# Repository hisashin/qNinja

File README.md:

# Open Source $300 Real Time PCR and LAMP machine "qNinja"

# $50 qLAMP machine "[qNinja Lite](https://github.com/hisashin/qNinjaLite)" is also available

## Reference Links
- [qNinja portal](https://qninja.hisa.dev)

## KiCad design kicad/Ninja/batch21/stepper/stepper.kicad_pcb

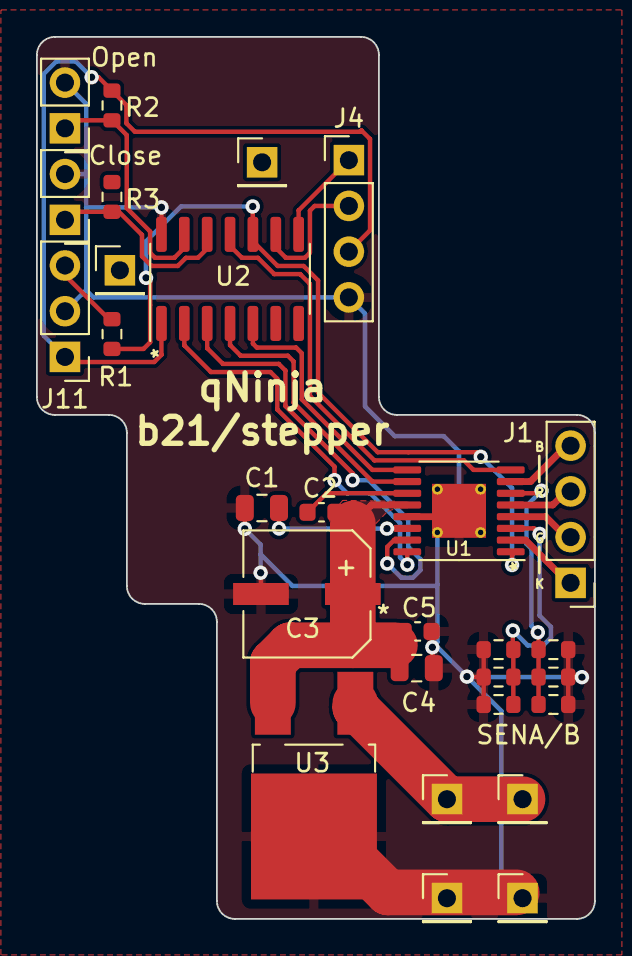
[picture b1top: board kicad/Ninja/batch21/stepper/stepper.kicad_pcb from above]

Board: 2 copper layers, 31.0 x 49.0 mm, 28 parts (0 on the bottom side), 23 nets.

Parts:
C1: 4.7uF; C_0805_2012Metric
C2, C5: 0.1uF; C_0603_1608Metric
C3: 100uF; 35TZV100M6.3X8
C4: 10uF; C_0805_2012Metric
J1: Conn_01x04_Male; PinHeader_1x04_P2.54mm_Vertical
J3, J5, J6, J7, J9, J10: Conn_01x01_Pin; PinHeader_1x01_P2.54mm_Vertical
J4: Conn_01x04_Pin; PinHeader_1x04_P2.54mm_Vertical
J11: Conn_01x03_Pin; PinHeader_1x03_P2.54mm_Vertical
J12, J13: Conn_01x02_Pin; PinHeader_1x02_P2.54mm_Vertical
R1, R2, R3: 4.7k; R_0603_1608Metric
RSENA1, RSENA2, RSENA3: R; R_0603_1608Metric
RSENB1, RSENB2, RSENB3: R; R_0603_1608Metric
U1: MP6507GF-Z; TSSOP-16-1EP_4.4x5mm_P0.65mm_EP3x3mm_ThermalVias
U2: ATtiny404-SS; SOIC-14_3.9x8.7mm_P1.27mm
U3: REG_TO252-3

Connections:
/3V3D: J4.3, J11.1, R2.2, U2.1 (VCC)
/12VB: J5.1, J6.1, U3.1 (VIN)
/AIN1: U1.16 (AIN1), U2.2 (PA4)
/AIN2: U1.15 (AIN2), U2.3 (PA5)
/BIN1: U1.10 (BIN2), U2.4 (PA6)
/BIN2: U1.9 (BIN1), U2.5 (PA7)
/DCLOSE: J13.1, R3.1, U2.12 (PA2)
/DOPEN: J12.1, R2.1, U2.13 (PA3)
/FAULT: U1.8 (FAULT), U2.11 (PA1)
/I2C_SCL: J4.2, U2.9 (PB0)
/I2C_SDA: J4.1, U2.8 (PB1)
/NSLEEP: R1.1, U1.1 (NSLEEP), U2.10 (~RESET/PA0)
/SENA: RSENA1.1, RSENA2.1, RSENA3.1, U1.3 (SENA)
/SENB: RSENB1.2, RSENB2.2, RSENB3.2, U1.6 (SENB)
/UPDI: J11.3, R1.2
/VIN: C2.2, C3.1, C4.1, C5.1, U1.12 (VIN), U3.2 (VOUT)
GND: C1.1, C3.2, C4.2, C5.2, J4.4, J9.1, J10.1, J11.2, J12.2, J13.2, RSENA1.2, RSENA2.2, RSENA3.2, RSENB1.1, RSENB2.1, RSENB3.1, U1.13 (GND), U1.17 (EPAD), U2.14 (GND), U3.3 (GND)
unnamed: J1.1, U1.2 (AOUT1)
unnamed: J1.2, U1.4 (AOUT2)
unnamed: J1.3, U1.5 (BOUT2)
unnamed: J1.4, U1.7 (BOUT1)
unnamed: C2.1, U1.11 (BST)
unnamed: C1.2, U1.14 (VDD)

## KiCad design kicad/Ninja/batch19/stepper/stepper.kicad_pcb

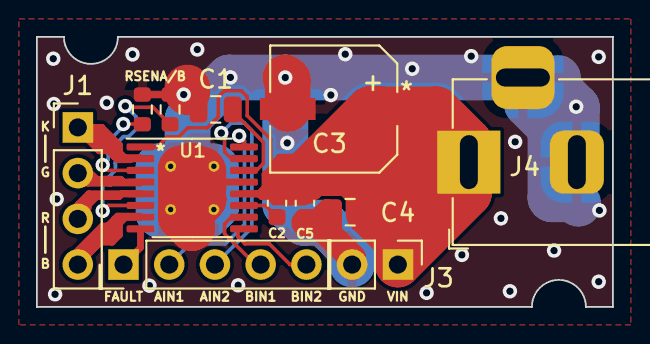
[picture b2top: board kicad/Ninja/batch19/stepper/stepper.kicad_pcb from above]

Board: 2 copper layers, 32.0 x 15.0 mm, 12 parts (0 on the bottom side), 15 nets.

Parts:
C1: 4.7uF; C_0805_2012Metric
C2: 0.1uF; C_0603_1608Metric
C3: 100uF; 35TZV100M6.3X8
C4: 10uF; C_0805_2012Metric
C5: 0.1uF(Low ESR ceramic); C_0603_1608Metric
J1: Conn_01x04_Male; PinHeader_1x04_P2.54mm_Vertical
J2: Conn_01x05_Male; PinHeader_1x05_P2.54mm_Vertical
J3: Conn_01x02_Male; PinHeader_1x02_P2.54mm_Vertical
J4: Barrel_Jack_Switch; BarrelJack_Horizontal
RSENA1: R; R_0603_1608Metric
RSENB1: R; R_0603_1608Metric
U1: MP6507GF-Z; TSSOP-16-1EP_4.4x5mm_P0.65mm_EP3x3mm_ThermalVias

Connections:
/AIN1: J2.2, U1.16 (AIN1)
/AIN2: J2.3, U1.15 (AIN2)
/BIN1: J2.4, U1.10 (BIN2)
/BIN2: J2.5, U1.9 (BIN1)
/FAULT: J2.1, U1.8 (FAULT)
/VIN: C2.2, C3.1, C4.1, C5.1, J3.1, J4.1, U1.1 (NSLEEP), U1.12 (VIN)
GND: C1.1, C3.2, C4.2, C5.2, J3.2, J4.2, J4.3, RSENA1.2, RSENB1.2, U1.13 (GND), U1.17 (EPAD)
unnamed: C1.2, U1.14 (VDD)
unnamed: C2.1, U1.11 (BST)
unnamed: J1.1, U1.2 (AOUT1)
unnamed: J1.2, U1.4 (AOUT2)
unnamed: J1.3, U1.5 (BOUT2)
unnamed: J1.4, U1.7 (BOUT1)
unnamed: RSENA1.1, U1.3 (SENA)
unnamed: RSENB1.1, U1.6 (SENB)

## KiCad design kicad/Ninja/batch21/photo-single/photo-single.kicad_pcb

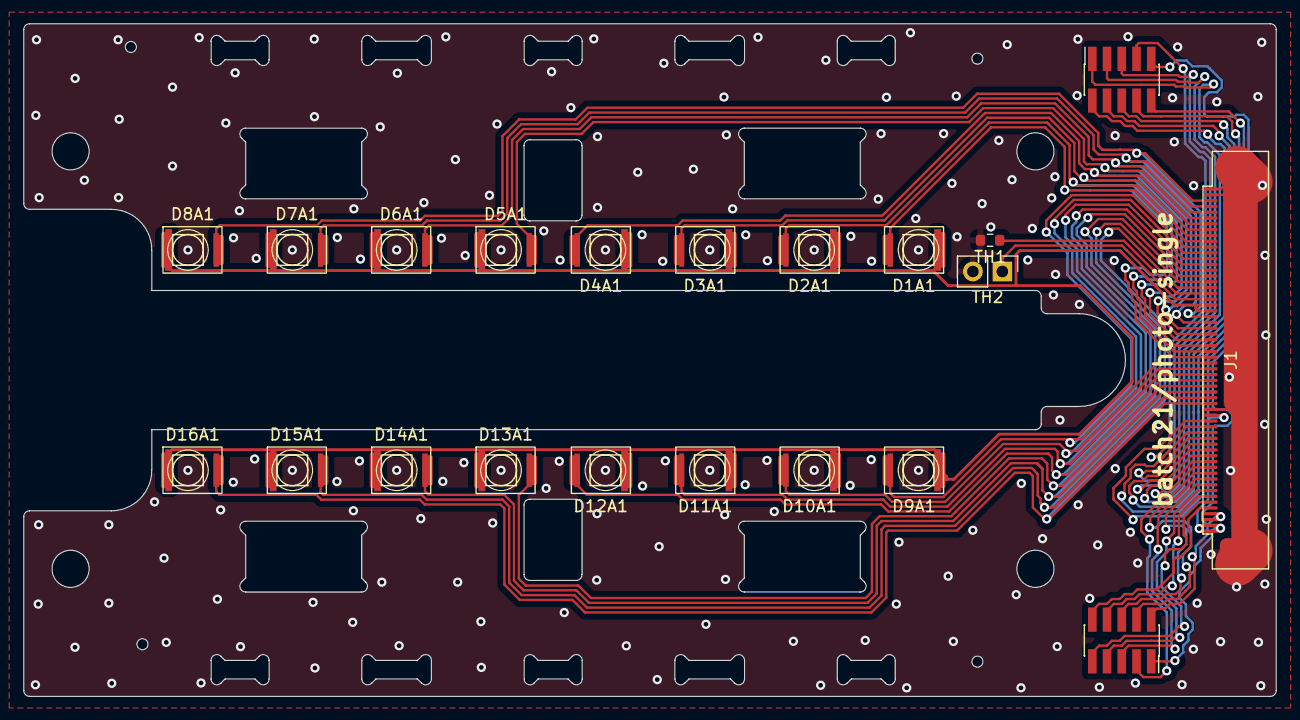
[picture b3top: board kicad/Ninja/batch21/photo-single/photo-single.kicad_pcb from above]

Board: 2 copper layers, 108.0 x 58.0 mm, 21 parts (0 on the bottom side), 38 nets.

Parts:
D1A1, D2A1, D3A1, D4A1, D5A1, D6A1, D7A1, D8A1, D9A1, D10A1, D11A1, D12A1, D13A1, D14A1, D15A1, D16A1: D_Photo; SFH2200_2201_2240
J1: Conn_01x60_Male; FFC_60_Ali_HUISHUNFA
JLN1: Conn_01x10_Male; PinSocket_2x05_P1.27mm_Vertical_SMD
JLS1: Conn_01x10_Male; PinSocket_2x05_P1.27mm_Vertical_SMD
TH1: Thermistor; R_0603_1608Metric
TH2: Thermistor; PinHeader_1x02_P2.54mm_Vertical

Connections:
/N_LED_OUT1: J1.20, JLN1.8
/N_LED_OUT2: J1.19, JLN1.7
/N_LED_OUT3: J1.18, JLN1.6
/N_LED_OUT4: J1.17, JLN1.5
/N_LED_OUT5: J1.16, JLN1.4
/N_LED_OUT6: J1.15, JLN1.3
/N_LED_OUT7: J1.14, JLN1.2
/N_LED_OUT8: J1.13, JLN1.1
/N_PD_OUT1: D1A1.2 (A), J1.31, J1.51
/N_PD_OUT3: D2A1.2 (A), J1.32, J1.52
/N_PD_OUT5: D3A1.2 (A), J1.33, J1.53
/N_PD_OUT7: D4A1.2 (A), J1.34, J1.54
/N_PD_OUT9: D5A1.2 (A), J1.35, J1.55
/N_PD_OUT11: D6A1.2 (A), J1.36, J1.56
/N_PD_OUT13: D7A1.2 (A), J1.37, J1.57
/N_PD_OUT15: D8A1.2 (A), J1.38, J1.58
/S_LED_OUT1: J1.12, JLS1.3
/S_LED_OUT2: J1.11, JLS1.4
/S_LED_OUT3: J1.10, JLS1.5
/S_LED_OUT4: J1.9, JLS1.6
/S_LED_OUT5: J1.8, JLS1.7
/S_LED_OUT6: J1.7, JLS1.8
/S_LED_OUT7: J1.6, JLS1.9
/S_LED_OUT8: J1.5, JLS1.10
/S_PD_OUT1: D9A1.2 (A), J1.30, J1.50
/S_PD_OUT3: D10A1.2 (A), J1.29, J1.49
/S_PD_OUT5: D11A1.2 (A), J1.28, J1.48
/S_PD_OUT7: D12A1.2 (A), J1.27, J1.47
/S_PD_OUT9: D13A1.2 (A), J1.26, J1.46
/S_PD_OUT11: D14A1.2 (A), J1.25, J1.45
/S_PD_OUT13: D15A1.2 (A), J1.24, J1.44
/S_PD_OUT15: D16A1.2 (A), J1.23, J1.43
GNDA: J1.22, J1.59, J1.60, J1.G1, J1.G2, TH1.2, TH2.2
GNDL: J1.1, J1.2, J1.21, JLN1.10, JLS1.1
unnamed: J1.41, TH2.1
unnamed: J1.42, TH1.1
VCCA: D1A1.1 (K), D2A1.1 (K), D3A1.1 (K), D4A1.1 (K), D5A1.1 (K), D6A1.1 (K), D7A1.1 (K), D8A1.1 (K), D9A1.1 (K), D10A1.1 (K), D11A1.1 (K), D12A1.1 (K), D13A1.1 (K), D14A1.1 (K), D15A1.1 (K), D16A1.1 (K), J1.39, J1.40
VCCL: J1.3, J1.4, JLN1.9, JLS1.2

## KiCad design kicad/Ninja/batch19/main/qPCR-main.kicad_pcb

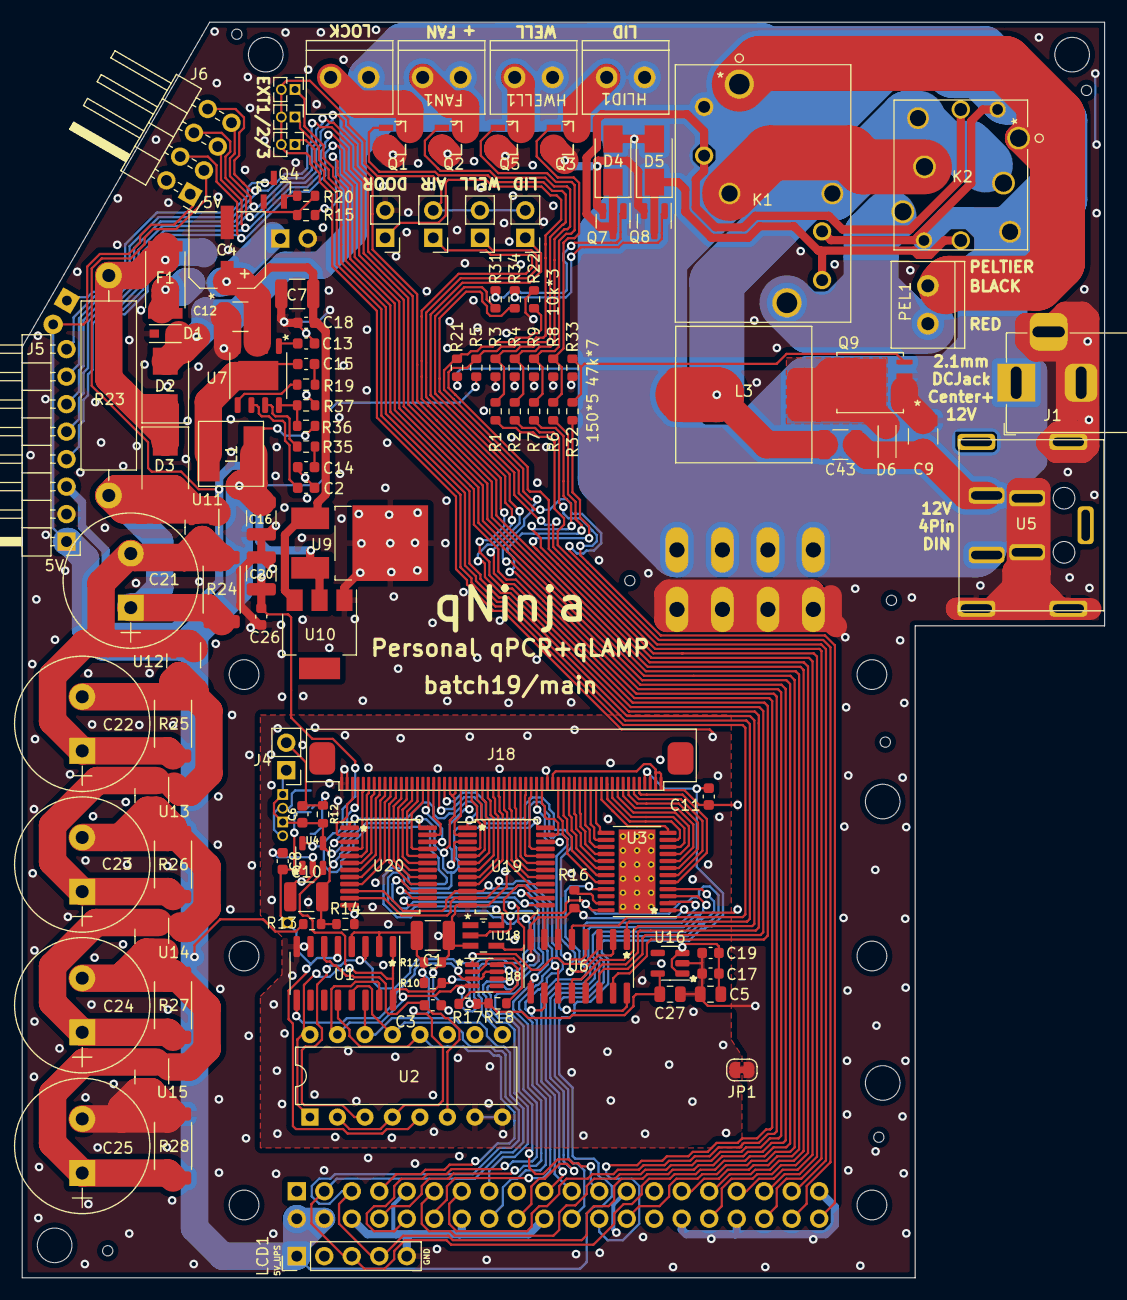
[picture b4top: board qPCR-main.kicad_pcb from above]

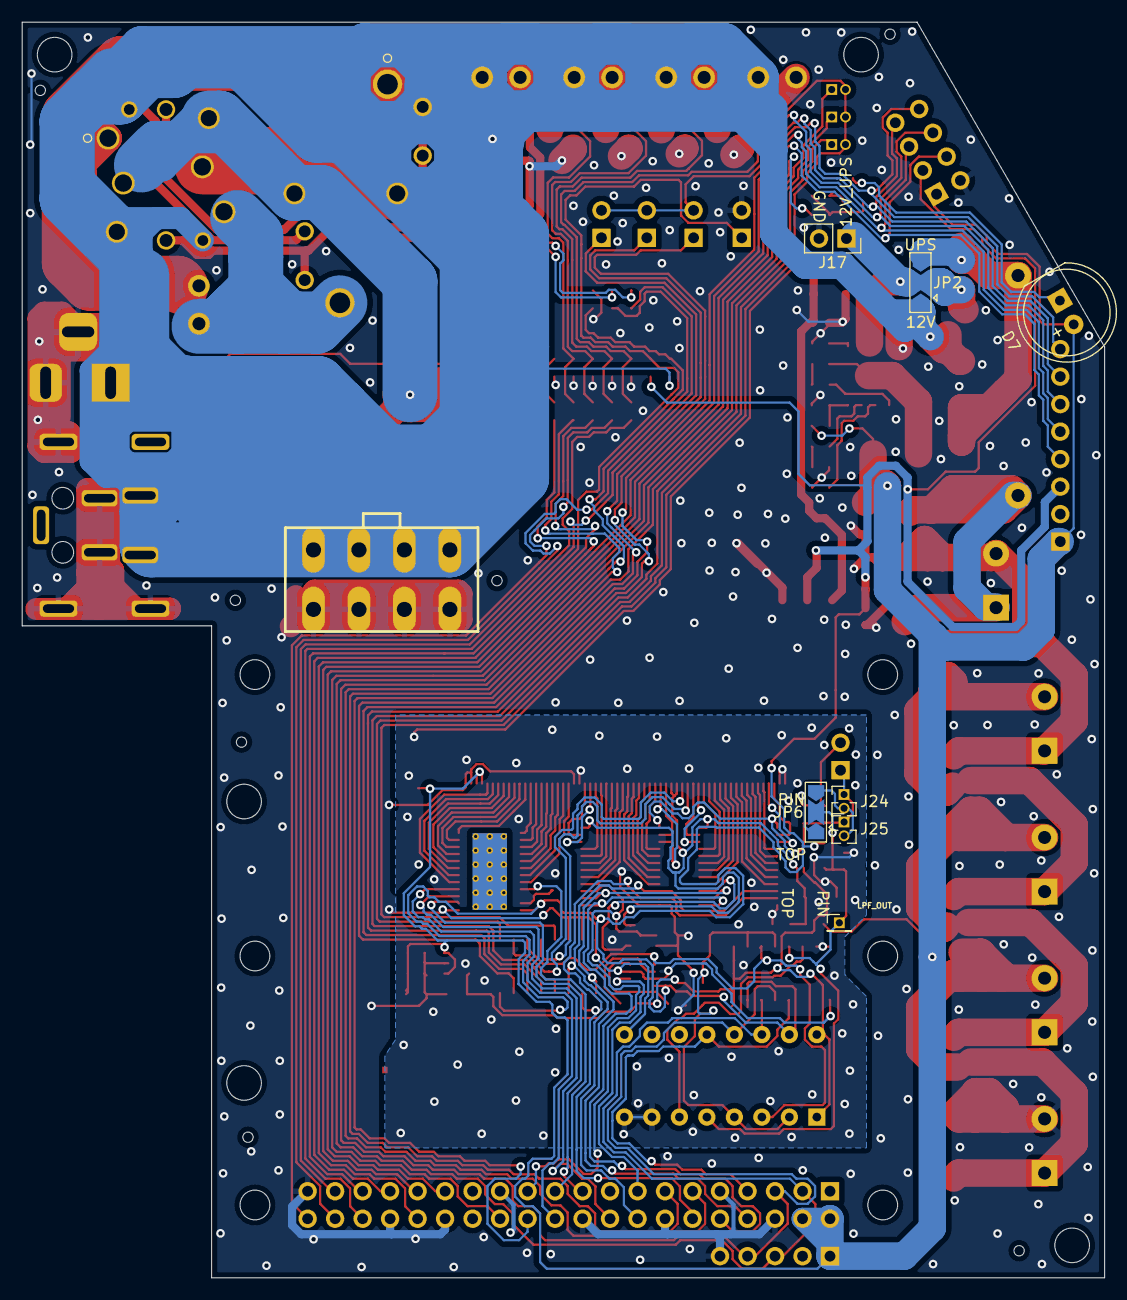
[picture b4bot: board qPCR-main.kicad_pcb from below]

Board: 2 copper layers, 100.0 x 116.0 mm, 129 parts (8 on the bottom side), 134 nets.

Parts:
C1, C7, C9, C10, C12, C16, C20, C43: 22uF; C_1210_3225Metric
C2, C3, C8, C11, C13, C17, C18, C26: 0.1uF; C_0603_1608Metric
C4: 100uF; 35TZV100M6.3X8
C5, C27: 4.7uF; C_0805_2012Metric
C6: 5pF; C_0603_1608Metric
C14, C15, C19: 0.01uF; C_0603_1608Metric
C21, C22, C23, C24, C25: 10F2.7V; CP_Radial_D12.5mm_P5.00mm
D1, D6: D_Schottky; MSS1P3L-M3&slash_89A
D2, D3: D; D_SMB
D4, D5: DIODE; D_SMA
D7: LED; LED_D8.0mm
F1: Fuse; R_2512
FAN1: Screw_Terminal_01x02; TB_SeeedOPL_320110028
HLID1: Screw_Terminal_01x02; TB_SeeedOPL_320110028
HWELL1: Screw_Terminal_01x02; TB_SeeedOPL_320110028
J1: Barrel_Jack_Switch; BarrelJack_Horizontal
J2: Raspberry_Pi_3A_Plus_wpi; Raspberry_Pi_3A+_3B+_4B_Zero_FaceDown_HDMI-R-NOSILK
J3: Conn_01x08_Male; ATX8
J4: Conn_01x02_Male; PinHeader_1x02_P2.54mm_Vertical
J5: Conn_01x08_Male; PinHeader_1x08_P2.54mm_Horizontal
J6: Conn_01x08_Male; PinHeader_2x04_P2.54mm_Horizontal
J17: Conn_01x02_Male; PinSocket_1x02_P2.54mm_Vertical
J18: Conn_01x60_Male; FFC_60_Ali_HUISHUNFA
J23: Conn_01x01_Male; PinHeader_1x01_P1.27mm_Vertical
J24, J25: Conn_01x02_Male; PinHeader_1x02_P1.27mm_Vertical
JP1: SolderJumper_2_Bridged; SolderJumper-2_P1.3mm_Bridged_RoundedPad1.0x1.5mm
JP2, JP6: Jumper_3_Open; SolderJumper-3_P2.0mm_Open_TrianglePad1.0x1.5mm
K1: EP2-3L3SAb
K2: EX2-2U1S
L1: 10uH; VLS6045EX-3R3N
L3: SRP1265C-220M; SRP1265C
LCD1: RPI_LCD_TOUCH_7INCH; PinHeader_1x05_P2.54mm_Vertical
LOCK1: Conn_01x02_Male; TB_SeeedOPL_320110028
PEL1: Screw_Terminal_01x02; TB_SeeedOPL_320110028
Q1, Q2, Q3, Q4, Q5: Q_NMOS_GSD; SOT95P240X112-3N
Q7, Q8: Q_NPN_BCE; SOT-23
Q9: SIRA88BDP-T1-GE3; PowerPAK_SO-8_Long
R1, R2, R6, R7, R15, R19, R32: 150; R_0603_1608Metric
R3, R4, R5, R8, R9, R20, R21, R33: 47k; R_0603_1608Metric
R10, R11, R18: 47k_HP; R_0603_1608Metric
R12: 10M; R_0603_1608Metric
R13, R22, R31, R34, R35, R37: 10k; R_0603_1608Metric
R14: 100k; R_0603_1608Metric
R16: 3.3k; R_0603_1608Metric
R17: 10k_HP; R_0603_1608Metric
R23: 8.2Ω 3W; R_Axial_DIN0516_L15.5mm_D5.0mm_P20.32mm_Horizontal
R24, R25, R26, R27, R28: 1k2W; R_2512_6332Metric
R36: 75k; R_0603_1608Metric
SW1: SW_Reed; PinHeader_1x02_P2.54mm_Vertical
TAIR1: Conn_01x02_Male; PinHeader_1x02_P2.54mm_Vertical
TEXT1, TEXT2, TEXT3: Conn_01x02_Male; PinHeader_1x02_P1.27mm_Vertical
TLID1: Conn_01x02_Male; PinHeader_1x02_P2.54mm_Vertical
TWELL1: Conn_01x02_Male; PinHeader_1x02_P2.54mm_Vertical
U1: NAU7802; SOIC-16_3.9x9.9mm_P1.27mm
U2: NAU7802; DIP-16_W7.62mm
U3: TLC5929; HTSSOP-24-1EP_4.4x7.8mm_P0.65mm_EP3.4x7.8mm_Mask2.4x4.68mm_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
U4: LMP7717MF_NOPB; SOT-23-5
U5: DIN4_PWR; DN4_PWR
U6: SN74LV4051A; SOIC-16_3.9x9.9mm_P1.27mm
U7: AOZ6600; AOZ6605PI-1
U8: TS12A12511DCNR; SOT-23-8-8.3mil
U9: REG_TO252-3
U10: LD1086DTTR; SOT-223
U11, U12, U13, U14, U15: TL431DBZ; SOT-23
U16: MCP1755T-3302E_OT; SOT-23-5
U18: SN74LVC1GU04DCKR; SN74LVC1GU04DBVR
U19, U20: CD74HC4067M96; SSOP-24_5.3x8.2mm_P0.65mm-0.83mil

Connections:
3V3A: C27.1, R10.1, R17.1, R18.1, U1.1 (REFP), U1.16 (AVDD), U2.1 (REFP), U2.16 (AVDD), U4.3 (IN+), U16.5 (VOUT)
3V3D: C20.1, C26.1, J5.3, J6.3, R5.1, U1.15 (DVDD), U2.15 (DVDD), U3.24 (VCC), U4.5 (V+), U6.16 (VCC), U8.4 (V+), U9.2 (VOUT), U10.2 (OUT)
5V_UPS: C5.1, C11.1, C16.2, C17.1, C19.1, D7.2 (A), J2.2 (5V), J2.4 (5V), J5.1, J6.1, J18.3, J18.4, L1.1, LCD1.1 (5V), R13.1, R36.1, U16.1 (VIN), U16.3 (SHDN)
12V: C9.1, C43.1, D1.1 (K), D2.2 (A), D4.2 (A), D5.2 (A), D6.1 (K), FAN1.1, HLID1.1, HWELL1.1, J1.1, J3.5, J3.6, J3.7, J3.8, JP2.1 (A), K1.2, K1.4, K1.6, K2.2, K2.5, K2.7, K2.9, LOCK1.1, R21.1, U5.1 (VIN1), U5.2 (VIN2)
12V_UPS: C4.1, C7.1, C12.2, C18.1, F1.1, J17.1, JP2.2 (C), U7.2 (EN), U7.3 (VIN), U9.1 (VIN), U10.3 (IN)
/FAN: J2.40 (GPIO29), R2.2
/LID_HEATER: J2.13 (GPIO2), R6.2
/Photo/AMP_OUT: C8.1, J23.1, JP6.2 (C), U1.5 (VIN2P), U2.5 (VIN2P), U4.1 (OUT)
/Photo/VBG: C3.1, U1.6 (VBG), U2.6 (VBG)
/PhotoMUX/MUX_SELECT_INV: U18.4, U20.15 (*E)
/PhotoMUX/N_PD_OUT1: J18.31, U19.9 (I0)
/PhotoMUX/N_PD_OUT2: J18.51, U20.9 (I0)
/PhotoMUX/N_PD_OUT3: J18.32, U19.8 (I1)
/PhotoMUX/N_PD_OUT4: J18.52, U20.8 (I1)
/PhotoMUX/N_PD_OUT5: J18.33, U19.7 (I2)
/PhotoMUX/N_PD_OUT6: J18.53, U20.7 (I2)
/PhotoMUX/N_PD_OUT7: J18.34, U19.6 (I3)
/PhotoMUX/N_PD_OUT8: J18.54, U20.6 (I3)
/PhotoMUX/N_PD_OUT9: J18.35, U19.5 (I4)
/PhotoMUX/N_PD_OUT10: J18.55, U20.5 (I4)
/PhotoMUX/N_PD_OUT11: J18.36, U19.4 (I5)
/PhotoMUX/N_PD_OUT12: J18.56, U20.4 (I5)
/PhotoMUX/N_PD_OUT13: J18.37, U19.3 (I6)
/PhotoMUX/N_PD_OUT14: J18.57, U20.3 (I6)
/PhotoMUX/N_PD_OUT15: J18.38, U19.2 (I7)
/PhotoMUX/N_PD_OUT16: J18.58, U20.2 (I7)
/PhotoMUX/S_PD_OUT1: J18.30, U19.16 (I15)
/PhotoMUX/S_PD_OUT2: J18.50, U20.16 (I15)
/PhotoMUX/S_PD_OUT3: J18.29, U19.17 (I14)
/PhotoMUX/S_PD_OUT4: J18.49, U20.17 (I14)
/PhotoMUX/S_PD_OUT5: J18.28, U19.18 (I13)
/PhotoMUX/S_PD_OUT6: J18.48, U20.18 (I13)
/PhotoMUX/S_PD_OUT7: J18.27, U19.19 (I12)
/PhotoMUX/S_PD_OUT8: J18.47, U20.19 (I12)
/PhotoMUX/S_PD_OUT9: J18.26, U19.20 (I11)
/PhotoMUX/S_PD_OUT10: J18.46, U20.20 (I11)
/PhotoMUX/S_PD_OUT11: J18.25, U19.21 (I10)
/PhotoMUX/S_PD_OUT12: J18.45, U20.21 (I10)
/PhotoMUX/S_PD_OUT13: J18.24, U19.22 (I9)
/PhotoMUX/S_PD_OUT14: J18.44, U20.22 (I9)
/PhotoMUX/S_PD_OUT15: J18.23, U19.23 (I8)
/PhotoMUX/S_PD_OUT16: J18.43, U20.23 (I8)
/Power/5V_SW: C15.2, L1.2, U7.EP (LX)
/SheetPeltier/PEL1: D4.1 (K), K1.3, K2.3, Q7.3 (C)
/SheetPeltier/PEL3: D5.1 (K), K1.7, K2.8, Q8.3 (C)
/SheetPeltier/PEL_BLK: K1.1, K2.1, PEL1.2
/SheetPeltier/PEL_RED: K1.8, K2.6, PEL1.1
/SheetPeltier/REG_D: D6.2 (A), L3.1, Q9.5 (D)
/WELL_HEATER: J2.33 (GPIO23/PWM1), R7.2
DIVIDED: C1.2, R10.2, R11.1, U1.2 (VIN1N), U1.4 (VIN2N), U2.2 (VIN1N), U2.4 (VIN2N)
DLOCK: J2.37 (GPIO25), R1.2
DOPEN: J2.35 (GPIO24), R5.2, SW1.1
GNDA: C1.1, C3.2, C8.2, C10.1, J18.22, J18.59, J18.60, JP1.2 (B), R11.2, R14.2, TAIR1.2, TEXT1.2, TEXT2.2, TEXT3.2, TLID1.2, TWELL1.2, U1.7 (REFN), U1.8 (AVSS), U2.7 (REFN), U2.8 (AVSS), U4.2 (V-), U18.3, U19.12 (GND), U20.12 (GND)
GNDD: C2.1, C4.2, C5.2, C7.2, C9.2, C11.2, C12.1, C13.1, C14.1, C16.1, C17.2, C18.2, C19.2, C20.2, C25.2, C26.2, C27.2, D1.2 (A), J1.2, J1.3, J2.6 (GND), J2.9 (GND), J2.14 (GND), J2.20 (GND), J2.25 (GND), J2.30 (GND), J2.34 (GND), J2.39 (GND), J3.1, J3.2, J3.3, J3.4, J5.2, J6.2, J17.2, J18.1, J18.2, J18.21, JP1.1 (A), LCD1.5 (GND), Q1.2 (S), Q2.2 (S), Q3.2 (S), Q4.2 (S), Q5.2 (S), Q7.2 (E), Q8.2 (E), Q9.1 (S), Q9.2 (S), Q9.3 (S), R3.1, R4.1, R8.1, R9.1, R16.1, R20.1, R22.2, R28.1, R33.2, R37.2, SW1.2, U1.9 (DVSS), U2.9 (DVSS), U3.1 (GND), U5.3 (GND), U5.4 (GND), U5.6 (CASE), U5.7 (CASE), U5.9 (CASE), U6.6 (INH), U6.7 (GND), U6.8 (GND), U7.4 (GND), U8.3 (GND), U8.7 (V-), U9.3 (GND), U10.1 (ADJ/GND), U15.3 (A), U16.2 (GND)
I2C_SCL: J2.5 (GPIO9/SCL1), J5.4, J6.4, LCD1.4 (SCL), U1.13 (SCLK), U2.13 (SCLK)
I2C_SDA: J2.3 (GPIO8/SDA1), J5.5, J6.5, LCD1.3 (SDA), U1.14 (SDIO), U2.14 (SDIO)
LED: J2.24 (GPIO10/CE0), R15.2
LED_BLANK: J2.21 (GPIO13/MISO), U3.21 (BLANK)
LED_C: D7.1 (K), Q4.3 (D)
LED_LAT: J2.22 (GPIO6), U3.4 (LAT)
LED_SPI_MOSI: J2.19 (GPIO12/MOSI), U3.2 (SIN)
LED_SPI_SCLK: J2.18 (GPIO5), U3.3 (SCLK)
MUX_S0: J2.16 (GPIO4), U6.11 (A), U19.10 (S0), U20.10 (S0)
MUX_S1: J2.12 (GPIO1/PWM0), U6.10 (B), U19.11 (S1), U20.11 (S1)
MUX_S2: J2.8 (GPIO15/TXD), U6.9 (C), U19.14 (S2), U20.14 (S2)
MUX_S3: J2.10 (GPIO16/RXD), U19.13 (S3), U20.13 (S3)
MUX_SELECT: J2.23 (GPIO14/SCLK), U18.2, U19.15 (*E)
NAU_DRDY: J2.7 (GPIO7), U1.12 (DRDY), U2.12 (DRDY)
N_LED_OUT1: J18.20, U3.20 (OUT15)
N_LED_OUT2: J18.19, U3.19 (OUT14)
N_LED_OUT3: J18.18, U3.18 (OUT13)
N_LED_OUT4: J18.17, U3.17 (OUT12)
N_LED_OUT5: J18.16, U3.16 (OUT11)
N_LED_OUT6: J18.15, U3.15 (OUT10)
N_LED_OUT7: J18.14, U3.14 (OUT9)
N_LED_OUT8: J18.13, U3.13 (OUT8)
unnamed: C2.2, U7.6 (VCC)
unnamed: C6.1, J4.2, JP6.1 (A), R12.2
unnamed: C13.2, U7.1 (SS)
unnamed: C14.2, R35.2
unnamed: C15.1, R19.2
unnamed: C21.1, D3.2 (A), R23.1, R24.2, U11.1 (K), U11.2 (REF)
unnamed: C21.2, C22.1, R24.1, R25.2, U11.3 (A), U12.1 (K), U12.2 (REF)
unnamed: C22.2, C23.1, R25.1, R26.2, U12.3 (A), U13.1 (K), U13.2 (REF)
unnamed: C23.2, C24.1, R26.1, R27.2, U13.3 (A), U14.1 (K), U14.2 (REF)
unnamed: C24.2, C25.1, R27.1, R28.2, U14.3 (A), U15.1 (K), U15.2 (REF)
unnamed: D2.1 (K), D3.1 (K), F1.2, JP2.3 (B), R23.2
unnamed: FAN1.2, Q2.3 (D)
unnamed: HLID1.2, Q3.3 (D)
unnamed: HWELL1.2, Q5.3 (D)
unnamed: J24.2, J25.2, JP6.3 (B)
unnamed: LOCK1.2, Q1.3 (D)
unnamed: Q1.1 (G), R1.1, R3.2
unnamed: Q2.1 (G), R2.1, R4.2
unnamed: Q3.1 (G), R6.1, R8.2
unnamed: Q4.1 (G), R15.1, R20.2
unnamed: Q5.1 (G), R7.1, R9.2
unnamed: Q7.1 (B), R31.1
unnamed: Q8.1 (B), R34.2
unnamed: Q9.4 (G), R32.1, R33.1
unnamed: R16.2, U3.23 (IREF)
unnamed: R17.2, U8.8 (NO)
unnamed: R18.2, U8.2 (NC)
unnamed: R19.1, U7.5 (BST)
unnamed: R35.1, U7.7 (COMP)
unnamed: R36.2, R37.1, U7.8 (FB)
PD_MUX_OUT: C6.2, J4.1, J24.1, J25.1, R12.1, U4.4 (IN-), U19.1 (COMMONINPUT/OUTPUT), U20.1 (COMMONINPUT/OUTPUT)
PD_TH1: J18.41, U6.2 (Y6)
PD_TH2: J18.42, U6.4 (Y7)
PEL_PWM: J2.32 (GPIO26/PWM0), R32.2
PEL_SWA: J2.36 (GPIO27), R31.2
PEL_SWB: J2.38 (GPIO28), R34.1
REG_OUT: C43.2, K1.5, K2.4, K2.10, L3.2
S_LED_OUT1: J18.12, U3.12 (OUT7)
S_LED_OUT2: J18.11, U3.11 (OUT6)
S_LED_OUT3: J18.10, U3.10 (OUT5)
S_LED_OUT4: J18.9, U3.9 (OUT4)
S_LED_OUT5: J18.8, U3.8 (OUT3)
S_LED_OUT6: J18.7, U3.7 (OUT2)
S_LED_OUT7: J18.6, U3.6 (OUT1)
S_LED_OUT8: J18.5, U3.5 (OUT0)
TACT1: J2.26 (GPIO11/CE1), J5.8, J6.8
TACT2: J2.29 (GPIO21), J5.7, J6.7
TACT3: J2.31 (GPIO22), J5.6, J6.6
THERM_AIR: TAIR1.1, U6.14 (Y1)
THERM_EXT1: TEXT1.1, U6.12 (Y3)
THERM_EXT2: TEXT2.1, U6.1 (Y4)
THERM_EXT3: TEXT3.1, U6.5 (Y5)
THERM_LID: TLID1.1, U6.15 (Y2)
THERM_MUX_OUT: U1.3 (VIN1P), U2.3 (VIN1P), U6.3 (COM), U8.1 (COM)
THERM_R_SWITCH: J2.15 (GPIO3), U8.6 (IN)
THERM_WELL: TWELL1.1, U6.13 (Y0)
VIN_SENSE: J2.11 (GPIO0), R21.2, R22.1
VOPT: C10.2, J18.39, J18.40, R13.2, R14.1, U18.5, U19.24 (VCC), U20.24 (VCC)

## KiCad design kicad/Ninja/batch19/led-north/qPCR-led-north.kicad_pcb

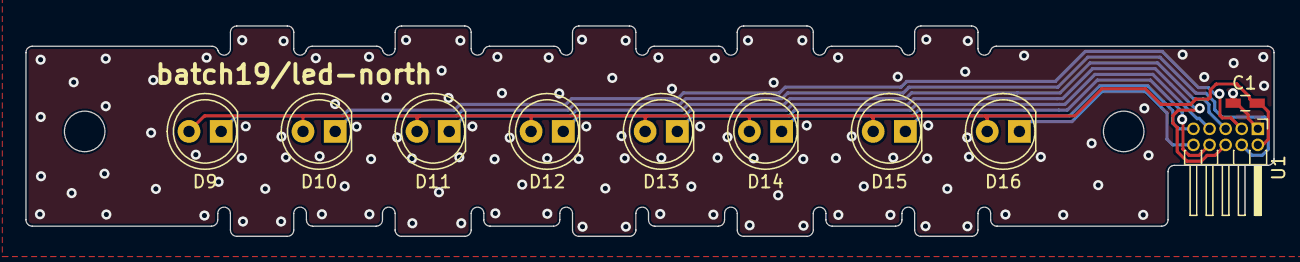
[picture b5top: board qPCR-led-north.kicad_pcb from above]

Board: 2 copper layers, 98.5 x 16.6 mm, 10 parts (0 on the bottom side), 10 nets.

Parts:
C1: C; C_0603_HandSoldering
D9, D10, D11, D12, D13, D14, D15, D16: LED; LED_D5.0mm
U1: Conn_01x10_Male; PinHeader_2x05_P1.27mm_Horizontal

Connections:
GND: C1.2, U1.1
OUT9: D9.1 (K), U1.3
OUT10: D10.1 (K), U1.4
OUT11: D11.1 (K), U1.5
OUT12: D12.1 (K), U1.6
OUT13: D13.1 (K), U1.7
OUT14: D14.1 (K), U1.8
OUT15: D15.1 (K), U1.9
OUT16: D16.1 (K), U1.10
VCC: C1.1, D9.2 (A), D10.2 (A), D11.2 (A), D12.2 (A), D13.2 (A), D14.2 (A), D15.2 (A), D16.2 (A), U1.2

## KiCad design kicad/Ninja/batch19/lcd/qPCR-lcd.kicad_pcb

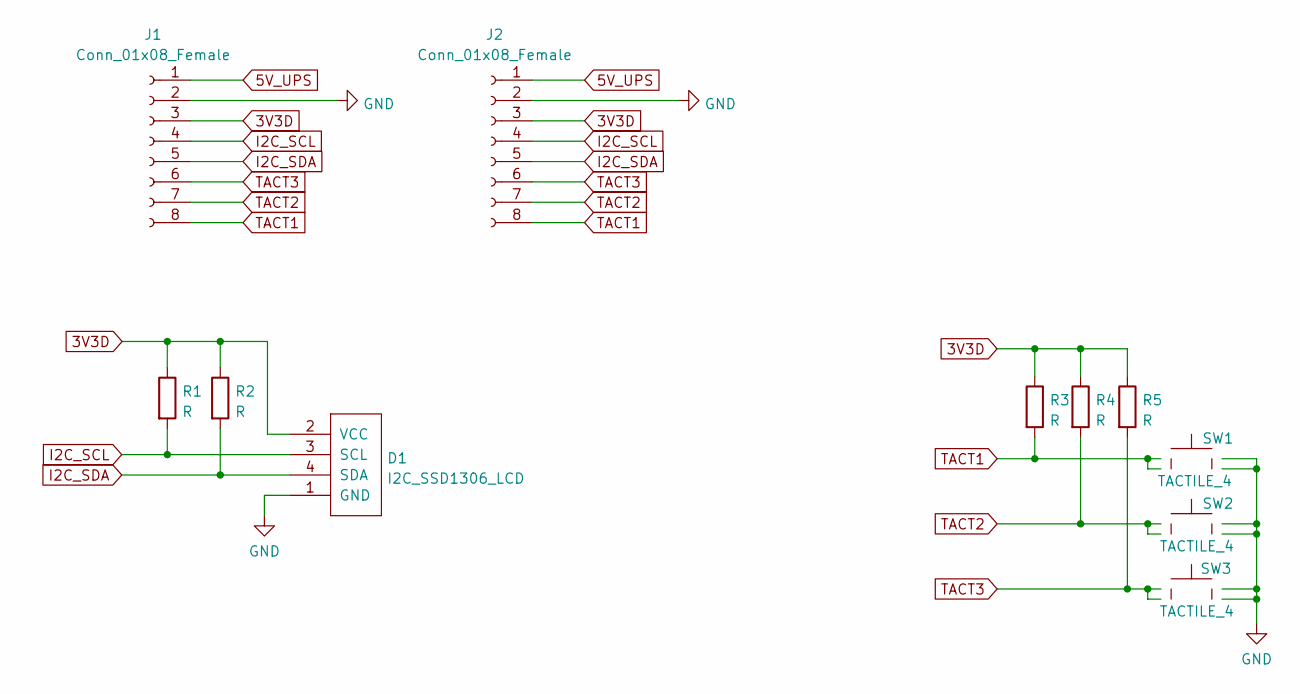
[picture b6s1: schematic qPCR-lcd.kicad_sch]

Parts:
D1: I2C_SSD1306_LCD; ALI_I2C_LCD
J1: Conn_01x08_Female; PinSocket_1x08_P2.54mm_Vertical
J2: Conn_01x08_Female; PinSocket_2x04_P2.54mm_Vertical
R1, R2, R3, R4, R5: R; R_0603_1608Metric
SW1, SW2, SW3: TACTILE_4; SW_TH_Tactile_Omron_B3F-10xx

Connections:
3V3D: D1.2 (VCC), J1.3, J2.3, R1.1, R2.1, R3.1, R4.1, R5.1
5V_UPS: J1.1, J2.1
GND: D1.1 (GND), J1.2, J2.2, SW1.3, SW1.4, SW2.3, SW2.4, SW3.3, SW3.4
I2C_SCL: D1.3 (SCL), J1.4, J2.4, R1.2
I2C_SDA: D1.4 (SDA), J1.5, J2.5, R2.2
TACT1: J1.8, J2.8, R3.2, SW1.1, SW1.2
TACT2: J1.7, J2.7, R4.2, SW2.1, SW2.2
TACT3: J1.6, J2.6, R5.2, SW3.1, SW3.2

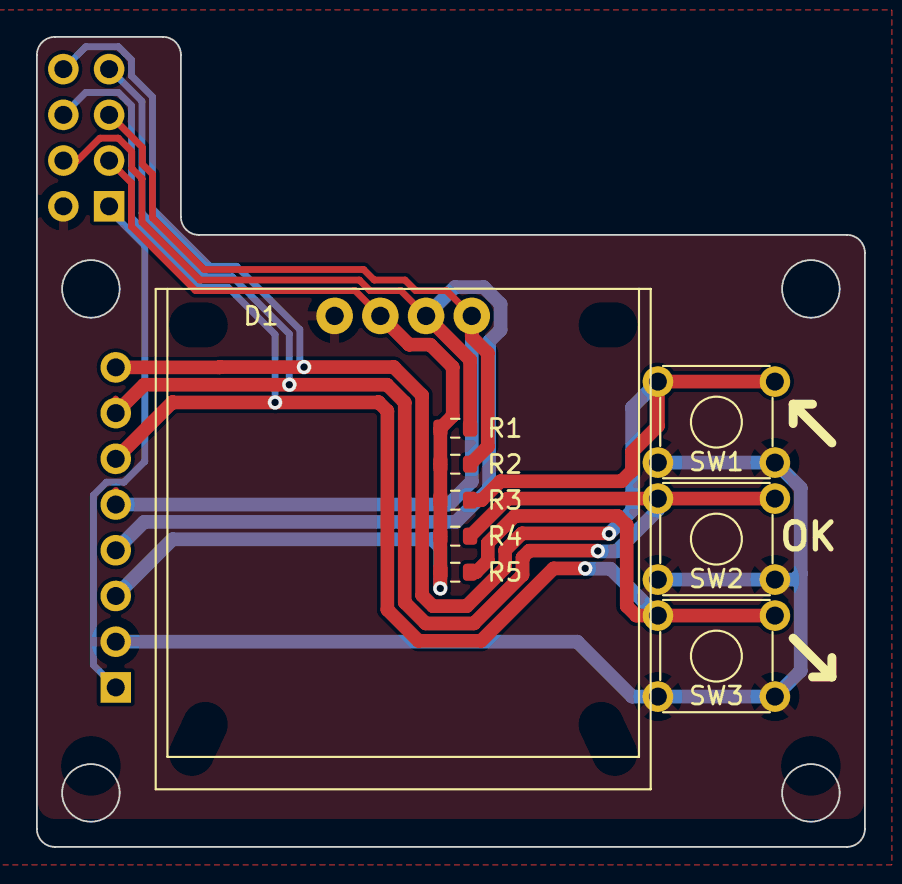
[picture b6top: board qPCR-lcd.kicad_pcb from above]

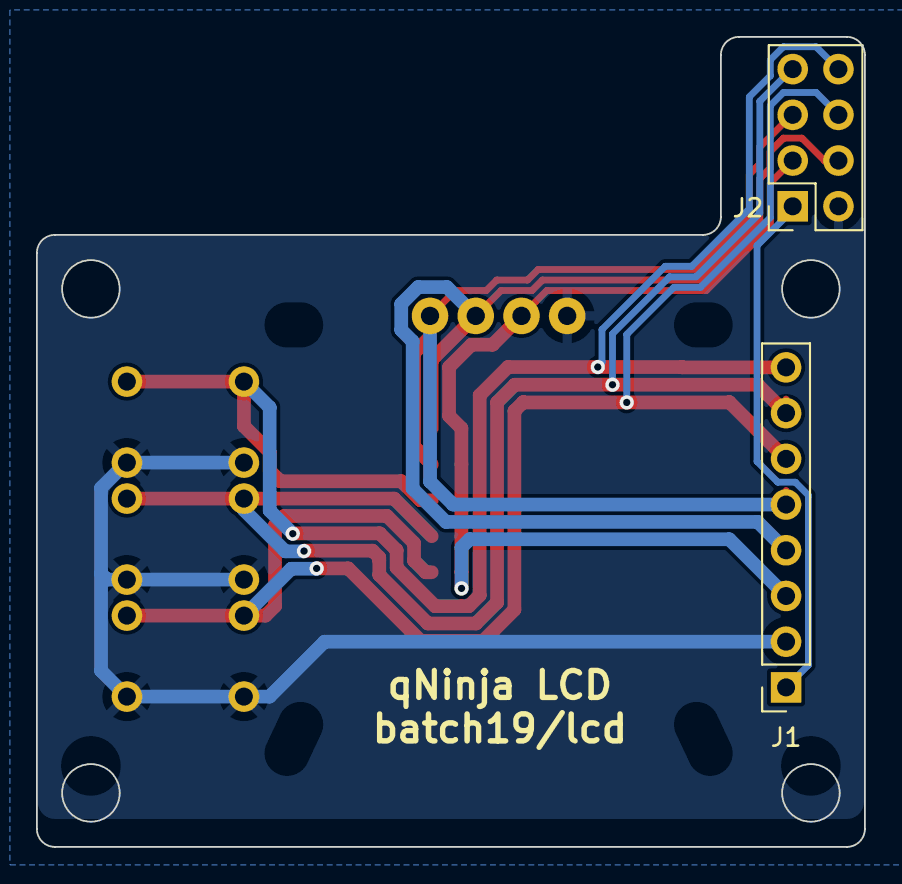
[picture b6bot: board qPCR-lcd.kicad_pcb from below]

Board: 2 copper layers, 46.0 x 45.0 mm, 11 parts (2 on the bottom side), 8 nets.

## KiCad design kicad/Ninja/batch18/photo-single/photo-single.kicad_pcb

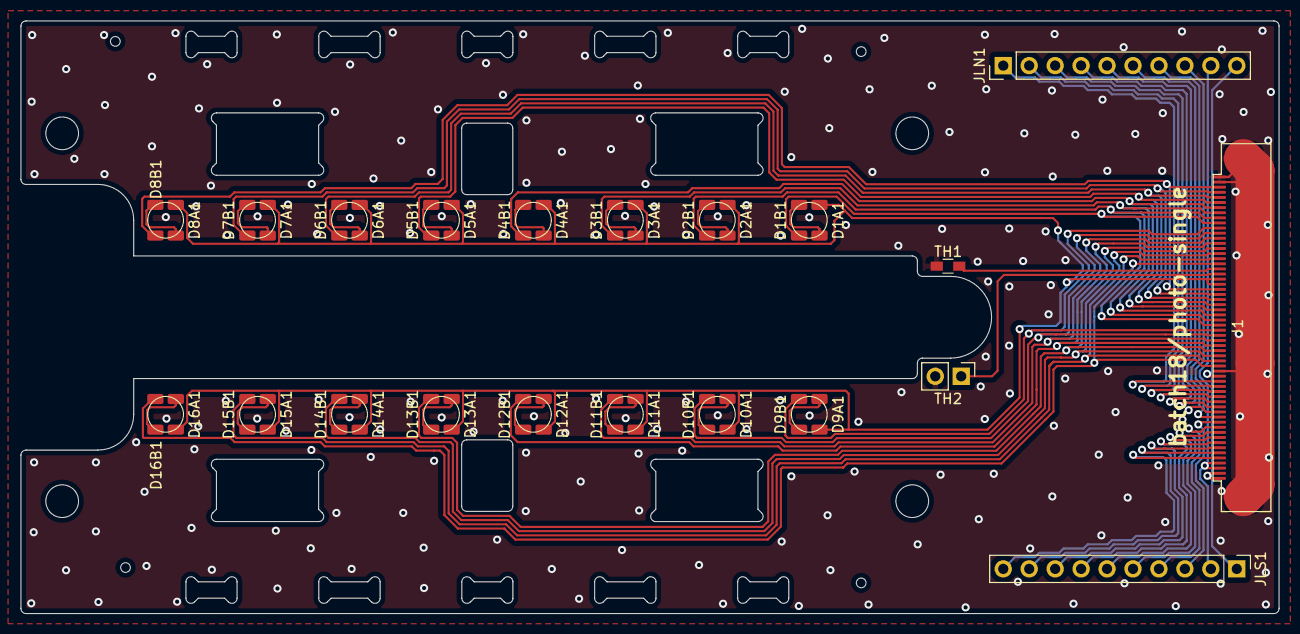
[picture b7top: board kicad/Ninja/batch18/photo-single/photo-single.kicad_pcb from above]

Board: 2 copper layers, 123.1 x 58.0 mm, 37 parts (0 on the bottom side), 54 nets.

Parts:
D1A1, D1B1, D2A1, D2B1, D3A1, D3B1, D4A1, D4B1, D5A1, D5B1, D6A1, D6B1, D7A1, D7B1, D8A1, D8B1, D9A1, D9B1, D10A1, D10B1, D11A1, D11B1, D12A1, D12B1, D13A1, D13B1, D14A1, D14B1, D15A1, D15B1, D16A1, D16B1: D_Photo; D_1206_nosilk
J1: Conn_01x60_Male; FFC_60_Ali_HUISHUNFA
JLN1: Conn_01x10_Male; Pin_Header_Straight_1x10_Pitch2.54mm
JLS1: Conn_01x10_Male; Pin_Header_Straight_1x10_Pitch2.54mm
TH1: Thermistor; R_0603_HandSoldering
TH2: Thermistor; PinHeader_1x02_P2.54mm_Vertical

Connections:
/N_LED_OUT1: J1.20, JLN1.1
/N_LED_OUT2: J1.19, JLN1.2
/N_LED_OUT3: J1.18, JLN1.3
/N_LED_OUT4: J1.17, JLN1.4
/N_LED_OUT5: J1.16, JLN1.5
/N_LED_OUT6: J1.15, JLN1.6
/N_LED_OUT7: J1.14, JLN1.7
/N_LED_OUT8: J1.13, JLN1.8
/N_PD_OUT1: D1B1.2 (A), J1.31, J1.51
/N_PD_OUT3: D2B1.2 (A), J1.32, J1.52
/N_PD_OUT5: D3B1.2 (A), J1.33, J1.53
/N_PD_OUT7: D4B1.2 (A), J1.34, J1.54
/N_PD_OUT9: D5B1.2 (A), J1.35, J1.55
/N_PD_OUT11: D6B1.2 (A), J1.36, J1.56
/N_PD_OUT13: D7B1.2 (A), J1.37, J1.57
/N_PD_OUT15: D8B1.2 (A), J1.38, J1.58
/S_LED_OUT1: J1.12, JLS1.3
/S_LED_OUT2: J1.11, JLS1.4
/S_LED_OUT3: J1.10, JLS1.5
/S_LED_OUT4: J1.9, JLS1.6
/S_LED_OUT5: J1.8, JLS1.7
/S_LED_OUT6: J1.7, JLS1.8
/S_LED_OUT7: J1.6, JLS1.9
/S_LED_OUT8: J1.5, JLS1.10
/S_PD_OUT1: D9B1.2 (A), J1.30, J1.50
/S_PD_OUT3: D10B1.2 (A), J1.29, J1.49
/S_PD_OUT5: D11B1.2 (A), J1.28, J1.48
/S_PD_OUT7: D12B1.2 (A), J1.27, J1.47
/S_PD_OUT9: D13B1.2 (A), J1.26, J1.46
/S_PD_OUT11: D14B1.2 (A), J1.25, J1.45
/S_PD_OUT13: D15B1.2 (A), J1.24, J1.44
/S_PD_OUT15: D16B1.2 (A), J1.23, J1.43
GNDA: J1.22, J1.59, J1.60, J1.G1, J1.G2, TH1.2, TH2.2
GNDL: J1.1, J1.2, J1.21, JLN1.10, JLS1.1
unnamed: D1A1.2 (A), D1B1.1 (K)
unnamed: D2A1.2 (A), D2B1.1 (K)
unnamed: D3A1.2 (A), D3B1.1 (K)
unnamed: D4A1.2 (A), D4B1.1 (K)
unnamed: D5A1.2 (A), D5B1.1 (K)
unnamed: D6A1.2 (A), D6B1.1 (K)
unnamed: D7A1.2 (A), D7B1.1 (K)
unnamed: D8A1.2 (A), D8B1.1 (K)
unnamed: D9A1.2 (A), D9B1.1 (K)
unnamed: D10A1.2 (A), D10B1.1 (K)
unnamed: D11A1.2 (A), D11B1.1 (K)
unnamed: D12A1.2 (A), D12B1.1 (K)
unnamed: D13A1.2 (A), D13B1.1 (K)
unnamed: D14A1.2 (A), D14B1.1 (K)
unnamed: D15A1.2 (A), D15B1.1 (K)
unnamed: D16A1.2 (A), D16B1.1 (K)
unnamed: J1.41, TH2.1
unnamed: J1.42, TH1.1
VCCA: D1A1.1 (K), D2A1.1 (K), D3A1.1 (K), D4A1.1 (K), D5A1.1 (K), D6A1.1 (K), D7A1.1 (K), D8A1.1 (K), D9A1.1 (K), D10A1.1 (K), D11A1.1 (K), D12A1.1 (K), D13A1.1 (K), D14A1.1 (K), D15A1.1 (K), D16A1.1 (K), J1.39, J1.40
VCCL: J1.3, J1.4, JLN1.9, JLS1.2

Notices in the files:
parts and their libraries:
Copyright 2021 Accelerated Designs. All rights reserved.
